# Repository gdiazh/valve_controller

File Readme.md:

Proyecto: Valve Controller
--------------------------------------

[TOC]

# Resumen

Controlador para válvulas latch.

# Recursos

## Hardware

Se utiliza un puente H para generar las seales de cierre/apertura. Se usa como microcontrolador un PIC16F628A y un módulo XBee para actuación remota.

## Software

TO DO

# Contenido del proyecto

To Do

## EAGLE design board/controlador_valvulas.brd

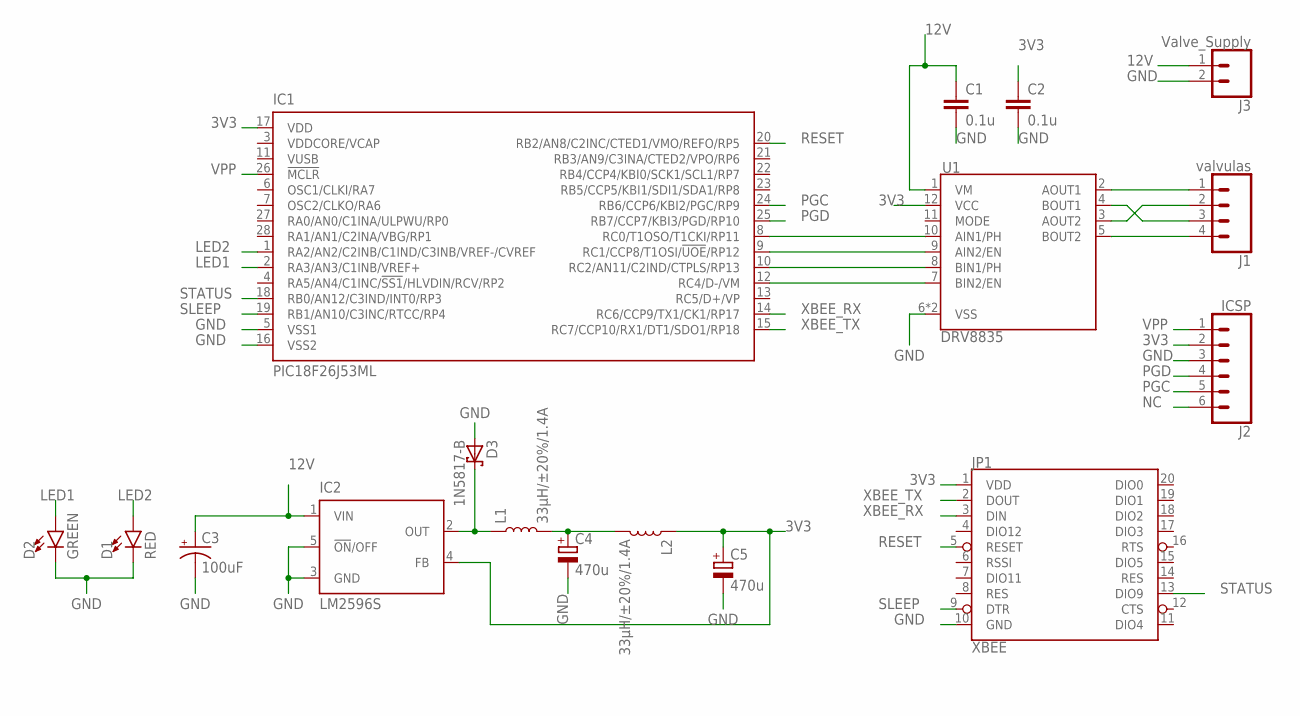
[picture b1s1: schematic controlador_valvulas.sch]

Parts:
C1, C2: 0.1u; C0805K
C3: 100uF; EIA7343
C4, C5: 470u; CT7343
D1: RED; LED-1206
D2: GREEN; LED-1206
D3: 1N5817-B; DO41-7.6
IC1: PIC18F26J53ML; QFN28-ML_6X6MM
IC2: LM2596S; TO263-5
J1: valvulas; 1X04
J2: ICSP; 1X06_LONGPADS
J3: Valve_Supply; 1X02
JP1: XBEE; XBEE-LONGPAD
L1, L2: 33µH/±20%/1.4A; SRN6045
U1: DRV8835; WSON-12

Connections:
3V3: C2.1, C5.+, IC1.17 (VDD), IC2.4 (FB), J2.2, JP1.1 (VDD), L2.1, U1.12 (VCC)
12V: C1.1, C3.A (+), IC2.1 (VIN), J3.1, U1.1 (VM)
GND: C1.2, C2.2, C3.C (-), C4.-, C5.-, D1.C, D2.C, D3.A, IC1.5 (VSS1), IC1.16 (VSS2), IC2.3 (GND), IC2.5 (!ON!/OFF), J2.3, J3.2, JP1.10 (GND), U1.6 (VSS), U1.PAD (VSS)
LED1: D2.A, IC1.2 (RA3/AN3/C1INB/VREF+)
LED2: D1.A, IC1.1 (RA2/AN2/C2INB/C1IND/C3INB/VREF-/CVREF)
unnamed: IC1.8 (RC0/T1OSO/T1CKI/RP11), U1.10 (AIN1/PH)
unnamed: IC1.9 (RC1/CCP8/T1OSI/!UOE!/RP12), U1.9 (AIN2/EN)
unnamed: IC1.10 (RC2/AN11/C2IND/CTPLS/RP13), U1.8 (BIN1/PH)
unnamed: IC1.12 (RC4/D-/VM), U1.7 (BIN2/EN)
unnamed: J1.1, U1.2 (AOUT1)
unnamed: J1.3, U1.4 (BOUT1)
unnamed: J1.2, U1.3 (AOUT2)
unnamed: J1.4, U1.5 (BOUT2)
unnamed: D3.C, IC2.2 (OUT), L1.1
unnamed: C4.+, L1.2, L2.2
NC: J2.6
PGC: IC1.24 (RB6/CCP6/KBI2/PGC/RP9), J2.5
PGD: IC1.25 (RB7/CCP7/KBI3/PGD/RP10), J2.4
RESET: IC1.20 (RB2/AN8/C2INC/CTED1/VMO/REFO/RP5), JP1.5 (RESET)
SLEEP: IC1.19 (RB1/AN10/C3INC/RTCC/RP4), JP1.9 (DTR)
STATUS: IC1.18 (RB0/AN12/C3IND/INT0/RP3), JP1.13 (DIO9)
VPP: IC1.26 (!MCLR), J2.1
XBEE_RX: IC1.14 (RC6/CCP9/TX1/CK1/RP17), JP1.3 (DIN)
XBEE_TX: IC1.15 (RC7/CCP10/RX1/DT1/SDO1/RP18), JP1.2 (DOUT)

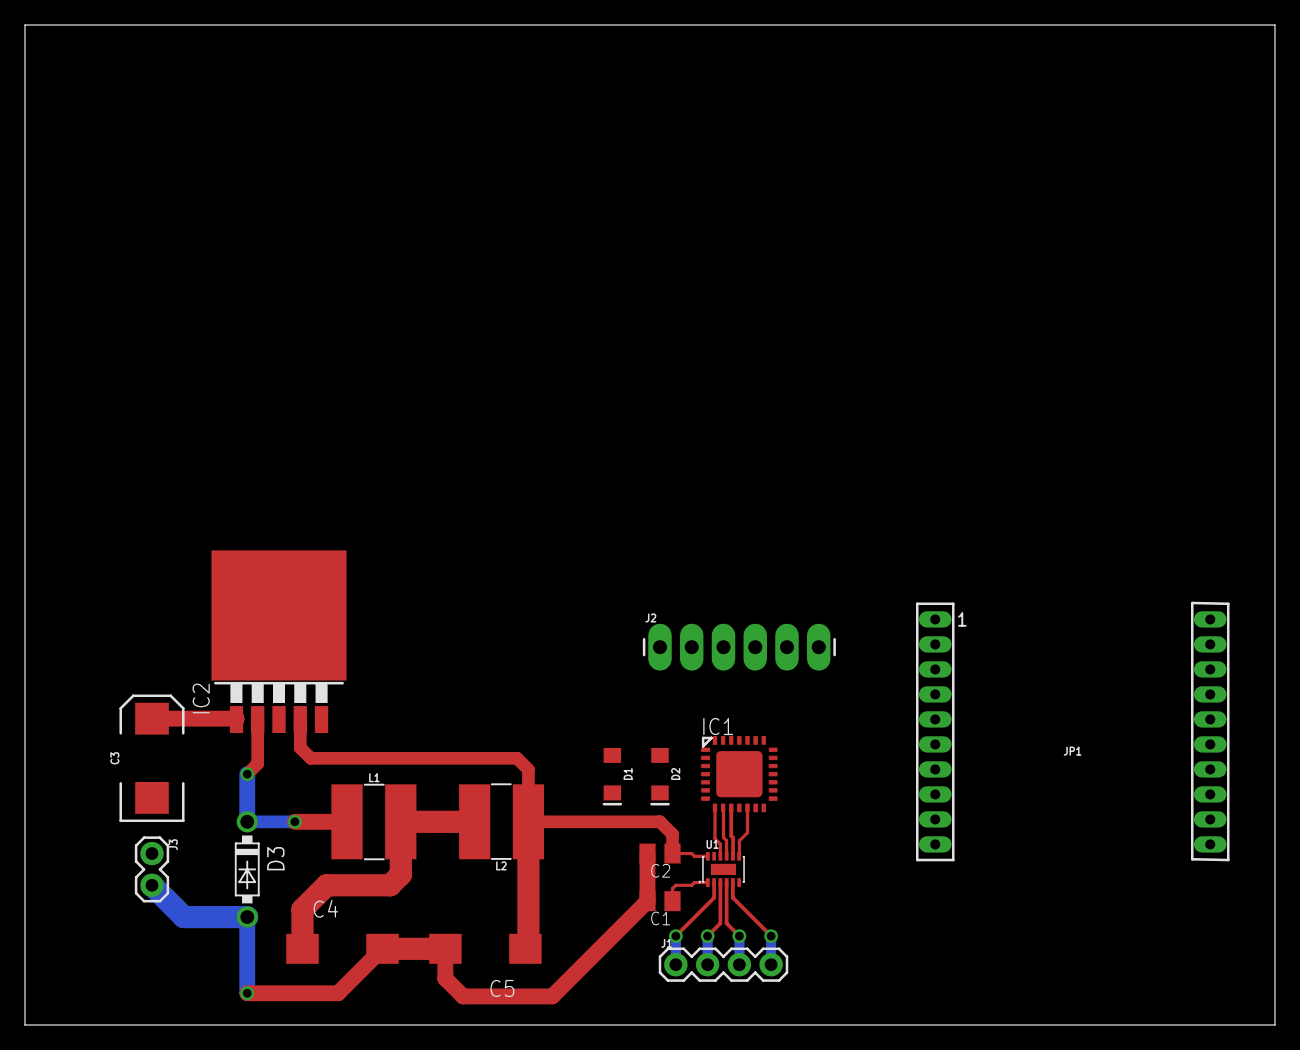
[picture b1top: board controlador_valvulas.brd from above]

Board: 2 copper layers, 100.0 x 80.0 mm, 17 parts (0 on the bottom side), 23 nets.

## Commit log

2017-05-25 start tracking the project

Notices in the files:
parts and their libraries:
SparkFun-IC-Special-Function: Licensing: Creative Commons ShareAlike 4.0 International - https://creativecommons.org/licenses/by-sa/4.0
